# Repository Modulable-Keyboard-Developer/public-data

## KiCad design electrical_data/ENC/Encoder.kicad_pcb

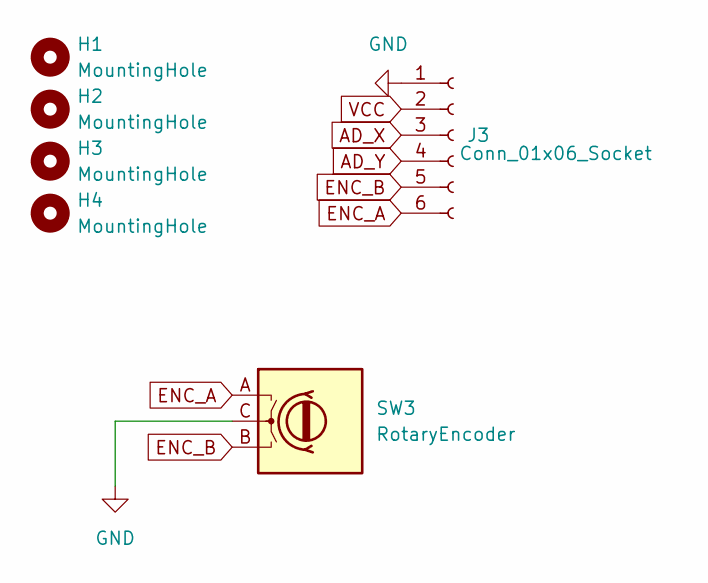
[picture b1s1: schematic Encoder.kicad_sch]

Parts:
H1, H2, H3, H4: MountingHole; m2_Screw_Hole
J3: Conn_01x06_Socket; Hirose_FH12-6S-0.5SH_1x06-1MP_P0.50mm_Horizontal
SW3: RotaryEncoder; RotaryEncoder_Alps_EC12E_Vertical_H20mm_custom

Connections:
AD_X: J3.3
AD_Y: J3.4
ENC_A: J3.6, SW3.A
ENC_B: J3.5, SW3.B
GND: J3.1, SW3.C
VCC: J3.2

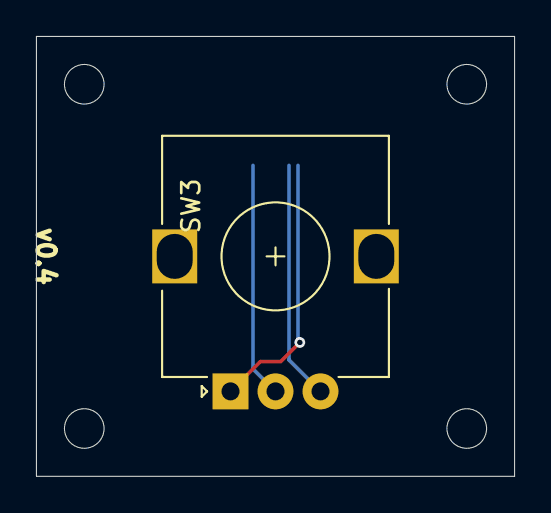
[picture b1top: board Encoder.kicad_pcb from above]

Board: 2 copper layers, 26.6 x 24.4 mm, 6 parts (1 on the bottom side), 3 nets.

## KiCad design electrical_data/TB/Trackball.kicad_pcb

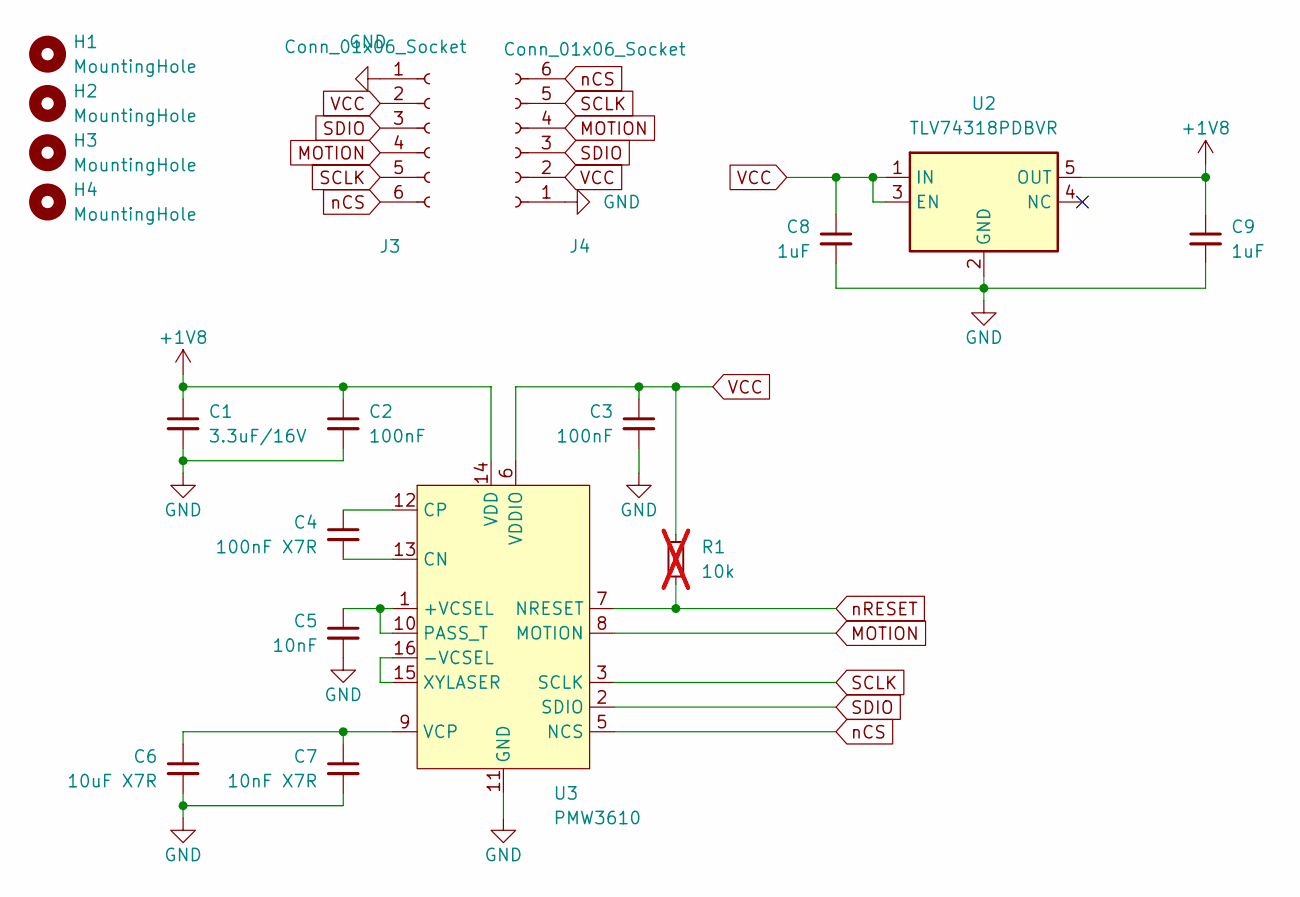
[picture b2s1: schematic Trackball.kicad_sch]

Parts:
C1: 3.3uF/16V; C_0603_1608Metric
C2, C3: 100nF; C_0603_1608Metric
C4: 100nF X7R; C_0603_1608Metric
C5: 10nF; C_0603_1608Metric
C6: 10uF X7R; C_0603_1608Metric
C7: 10nF X7R; C_0603_1608Metric
C8, C9: 1uF; C_0603_1608Metric
H1, H2, H3, H4: MountingHole; m2_Screw_Hole
J3, J4: Conn_01x06_Socket; Hirose_FH12-6S-0.5SH_1x06-1MP_P0.50mm_Horizontal
R1: 10k; R_0603_1608Metric; not fitted
U2: TLV74318PDBVR; SOT-23-5_HandSoldering
U3: PMW3610; PMW3610DM-SUDU 16Pin

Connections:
+1V8: C1.1, C2.1, C9.1, U2.5 (OUT), U3.14 (VDD)
GND: C1.2, C2.2, C3.2, C5.2, C6.2, C7.2, C8.2, C9.2, J3.1, J4.1, U2.2 (GND), U3.11 (GND)
MOTION: J3.4, J4.4, U3.8 (MOTION)
unnamed: C5.1, U3.1 (+VCSEL), U3.10 (PASS_T)
unnamed: U3.15 (XYLASER), U3.16 (-VCSEL)
unnamed: C4.2, U3.13 (CN)
unnamed: C4.1, U3.12 (CP)
unnamed: C6.1, C7.1, U3.9 (VCP)
SCLK: J3.5, J4.5, U3.3 (SCLK)
SDIO: J3.3, J4.3, U3.2 (SDIO)
VCC: C3.1, C8.1, J3.2, J4.2, R1.1, U2.1 (IN), U2.3 (EN), U3.6 (VDDIO)
nCS: J3.6, J4.6, U3.5 (NCS)
nRESET: R1.2, U3.7 (NRESET)

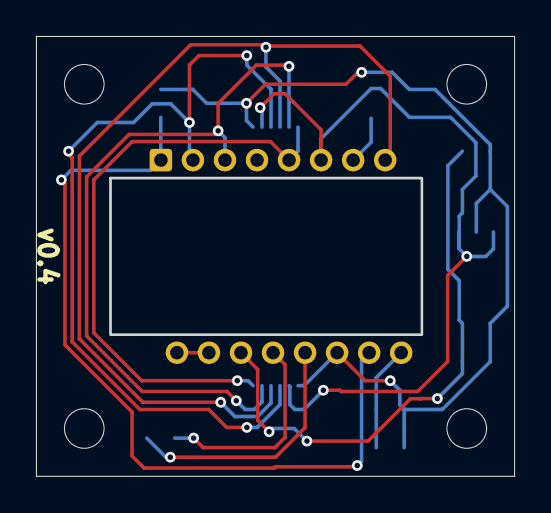
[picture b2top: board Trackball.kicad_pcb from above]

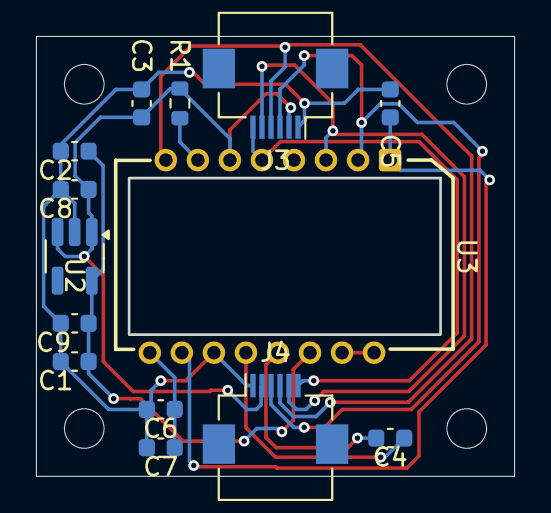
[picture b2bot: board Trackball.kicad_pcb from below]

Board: 2 copper layers, 26.5 x 24.3 mm, 18 parts (14 on the bottom side), 13 nets.

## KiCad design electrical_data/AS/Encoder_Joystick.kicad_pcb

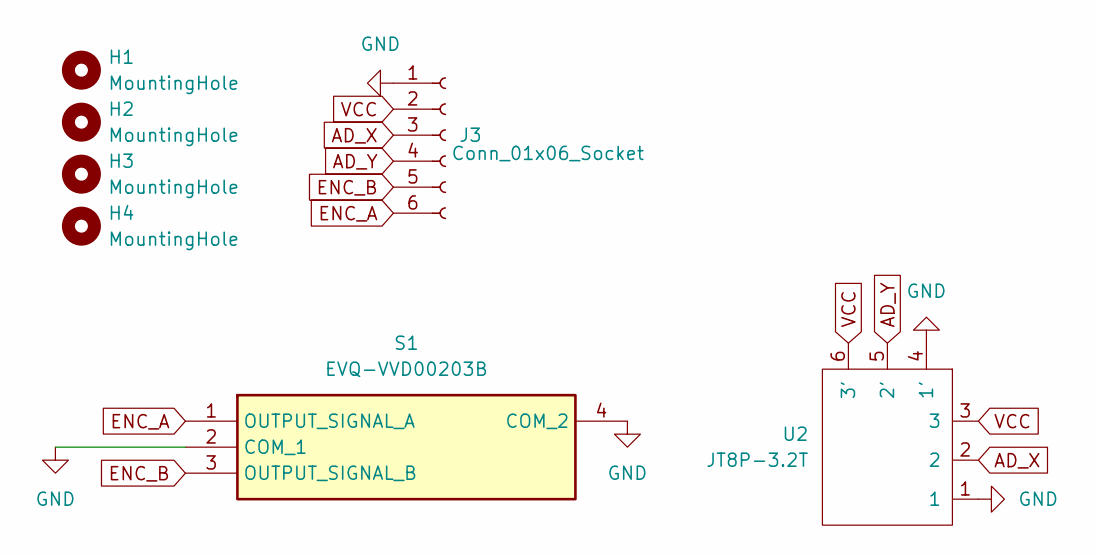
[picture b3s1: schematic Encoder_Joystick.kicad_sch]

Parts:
H1, H2, H3, H4: MountingHole; m2_Screw_Hole
J3: Conn_01x06_Socket; Hirose_FH12-6S-0.5SH_1x06-1MP_P0.50mm_Horizontal
S1: EVQ-VVD00203B; EVQVVD00203B; Mouser Part Number 667-EVQ-VVD00203B
U2: JT8P-3.2T

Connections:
AD_X: J3.3, U2.2
AD_Y: J3.4, U2.5 (2')
ENC_A: J3.6, S1.1 (OUTPUT_SIGNAL_A)
ENC_B: J3.5, S1.3 (OUTPUT_SIGNAL_B)
GND: J3.1, S1.2 (COM_1), S1.4 (COM_2), U2.1, U2.4 (1')
VCC: J3.2, U2.3, U2.6 (3')

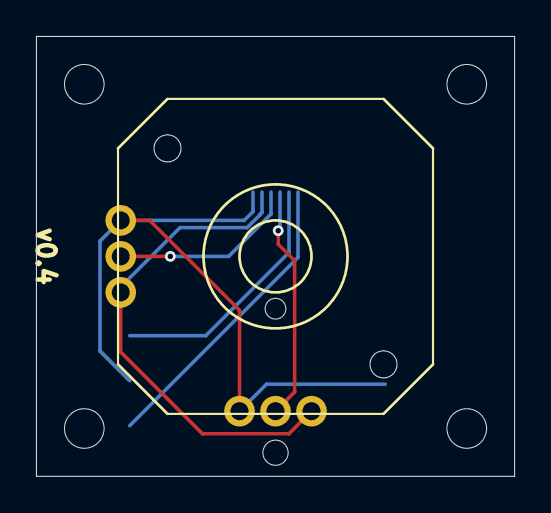
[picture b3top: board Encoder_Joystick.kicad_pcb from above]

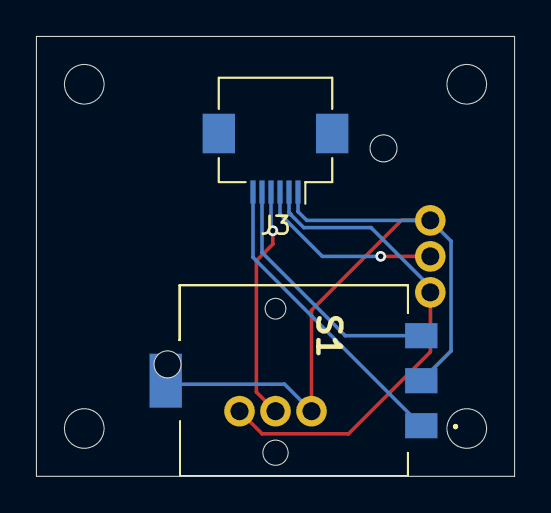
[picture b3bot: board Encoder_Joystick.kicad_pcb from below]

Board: 2 copper layers, 26.6 x 24.4 mm, 7 parts (2 on the bottom side), 6 nets.

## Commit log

2025-10-03 add: licence
